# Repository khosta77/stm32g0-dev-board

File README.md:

<h1 align="center">g0_dev_board</h1>

<p align="center">
  Открытая отладочная плата на STM32G0 для разработки
  <a href="https://github.com/khosta77/stm32-sdk">stm32-sdk</a>
  (C++20, только CMSIS, без HAL).
</p>

<p align="center">

</p>

> **Прототип.** Плата ещё не изготавливалась и не проверялась в железе.
> Проект прошёл ERC и DRC, но перед заказом сверьте стек слоёв и ограничения
> выбранного завода (см. раздел «Производство»).

## Назначение

Плата для обкатки драйверов и методологии SDK на STM32G0. Расширения
подключаются через шилды Arduino Uno R3 (CNC Shield V3, модули GSM/Wi-Fi),
все сигналы МК выведены на две гребёнки для логического анализатора.

- Встроенный программатор ST-LINK/V2-1-совместимый (DAPLink или Black Magic Probe)
- USB-UART на USART1, через него же работает ROM-загрузчик STM32G0
- Ethernet 10/100 на W5500, флэш 32 Мбит и microSD на общей шине SPI2
- Два датчика температуры TMP100: на верхней и нижней стороне платы
- Перемычки как на Nucleo: измерение тока МК (JP_IDD), отключение программатора

## Основные характеристики

| Параметр | Значение |
| --- | --- |
| МК | STM32G0B1CCT6 (LQFP-48), pin-to-pin совместим с STM32G071CBT6 |
| Программатор | STM32F103CBT6, USB Mini-B (J201), SWD на МК через JP_SWD 2x3 |
| USB-UART | FT232RL, USB Mini-B (J301) |
| Ethernet | W5500 + RJ45 HR911105A (магнитика в разъёме) |
| Память | W25Q32JVSSIQ (4 МБ) + microSD (Hirose DM3AT), общая SPI2 |
| Датчики | 2x TMP100 на I2C1 (0x4E, 0x4A) |
| Питание | от любого из двух USB через диоды Шоттки, LDO AP7361C-33E на 3.3 В |
| Расширение | разъёмы Arduino Uno R3 (без ICSP), 2 гребёнки ЛА 1x27 |
| Плата | 80 x 114 мм, 4 слоя: сигнал / GND / GND / сигнал |

Полная таблица назначения выводов МК — на листе `scheme/cpu.kicad_sch`
(и в [PDF схемы](docs/schematic.pdf)). Подписи выводов гребёнок ЛА нанесены
на шелкографию в формате «сигнал + порт МК».

## Содержимое репозитория

- `g0_dev_board.kicad_pro`, `g0_dev_board.kicad_sch`, `scheme/` — схема
  (KiCad 10, 8 листов)
- `g0_dev_board.kicad_pcb`, `g0_dev_board.kicad_dru` — плата и
  дополнительные правила DRC
- `g0_dev_board.kicad_sym`, `g0_dev_board.pretty/` — проектные библиотеки
- [`manufacturing/`](manufacturing/) — Gerber, сверловка, BOM и CPL в формате JLCPCB
- [`docs/`](docs/) — [PDF схемы](docs/schematic.pdf) и изображение платы
- [`scripts/export_manufacturing.py`](scripts/export_manufacturing.py) —
  генерация всех выгрузок одной командой
- [`RULES.md`](RULES.md) — правила расстановки и трассировки платы
- [`CLAUDE.md`](CLAUDE.md) — состав, соглашения проекта, нюансы для прошивки

## Производство

Файлы в `manufacturing/` подготовлены под JLCPCB и подходят большинству
заводов:

- `gerber/` — медь F/In1/In2/B, маска, паста, шелкография, контур,
  сверловка PTH/NPTH (Excellon) с картами отверстий;
- `BOM-g0_dev_board.csv` — колонки `Comment, Designator, Footprint, LCSC Part #`;
- `CPL-g0_dev_board.csv` — колонки `Designator, Mid X, Mid Y, Layer, Rotation`.

Перед заказом:

- **Стек и ограничения завода.** Переходные отверстия 0.4/0.3 мм, зазор
  0.2 мм, дорожки от 0.3 мм. Ширины дифпар USB (90 Ом) и MDI (100 Ом)
  нужно сверить со стеком выбранного завода.
- **Нижняя сторона.** U602 и C602 стоят на нижней стороне: при заводском
  монтаже нужна сборка второй стороны, иначе их паяют вручную.
- **Коды LCSC не заданы** для J201/J301 (USB Mini-B), J805/J806 (гребёнки 1x27)
  и JP801 (2x3) — подберите их или ставьте эти разъёмы вручную.
- **Не устанавливаются (DNP):** C109, C301, C701, R703 — в BOM и CPL их нет.
- **Повороты в CPL** взяты из KiCad. Для части корпусов нулевой угол JLCPCB
  отличается от KiCad — проверьте ориентацию в предпросмотре сборки на
  сайте завода.

## Лицензия

Оригинальные исходники проекта распространяются под
[CERN Open Hardware Licence Version 2 - Permissive](LICENSE) (CERN-OHL-P v2).
Источник: <https://github.com/khosta77/stm32g0-dev-board>.

Символы и посадочные места из библиотек KiCad распространяются на своих
условиях — см. [NOTICE](NOTICE) и [THIRD-PARTY-NOTICES.md](THIRD-PARTY-NOTICES.md).
Изменения проекта записываются в [CHANGES.txt](CHANGES.txt), авторы — в
[AUTHORS.md](AUTHORS.md), порядок участия — в [CONTRIBUTING.md](CONTRIBUTING.md).

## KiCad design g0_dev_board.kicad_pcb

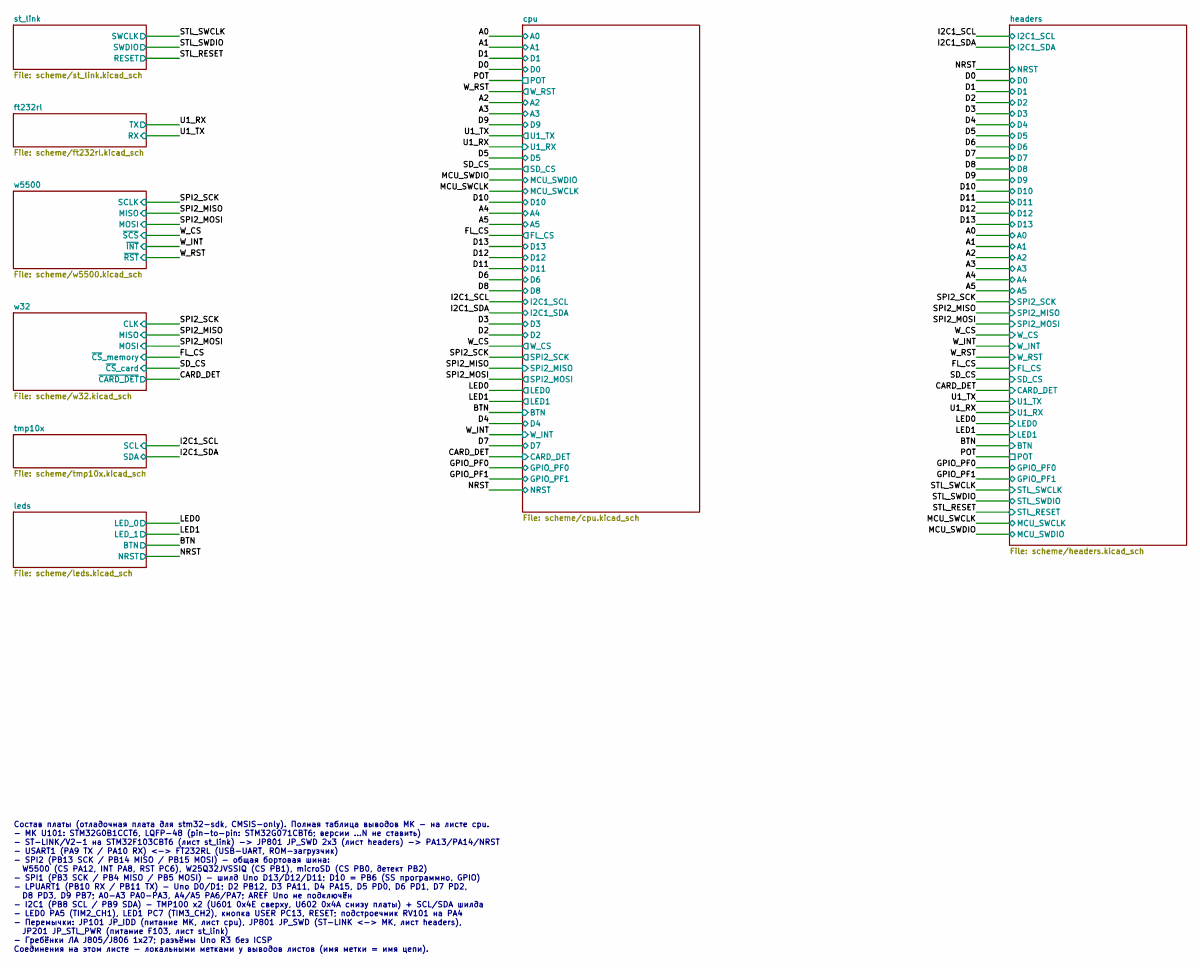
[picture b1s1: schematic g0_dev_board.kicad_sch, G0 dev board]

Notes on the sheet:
Состав платы (отладочная плата для stm32-sdk, CMSIS-only). Полная таблица выводов МК - на листе cpu. - МК U101: STM32G0B1CCT6, LQFP-48 (pin-to-pin: STM32G071CBT6; версии ...N не ставить) - ST-LINK/V2-1 на STM32F103CBT6 (лист st_link) -> JP801 JP_SWD 2x3 (лист headers) -> PA13/PA14/NRST - USART1 (PA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

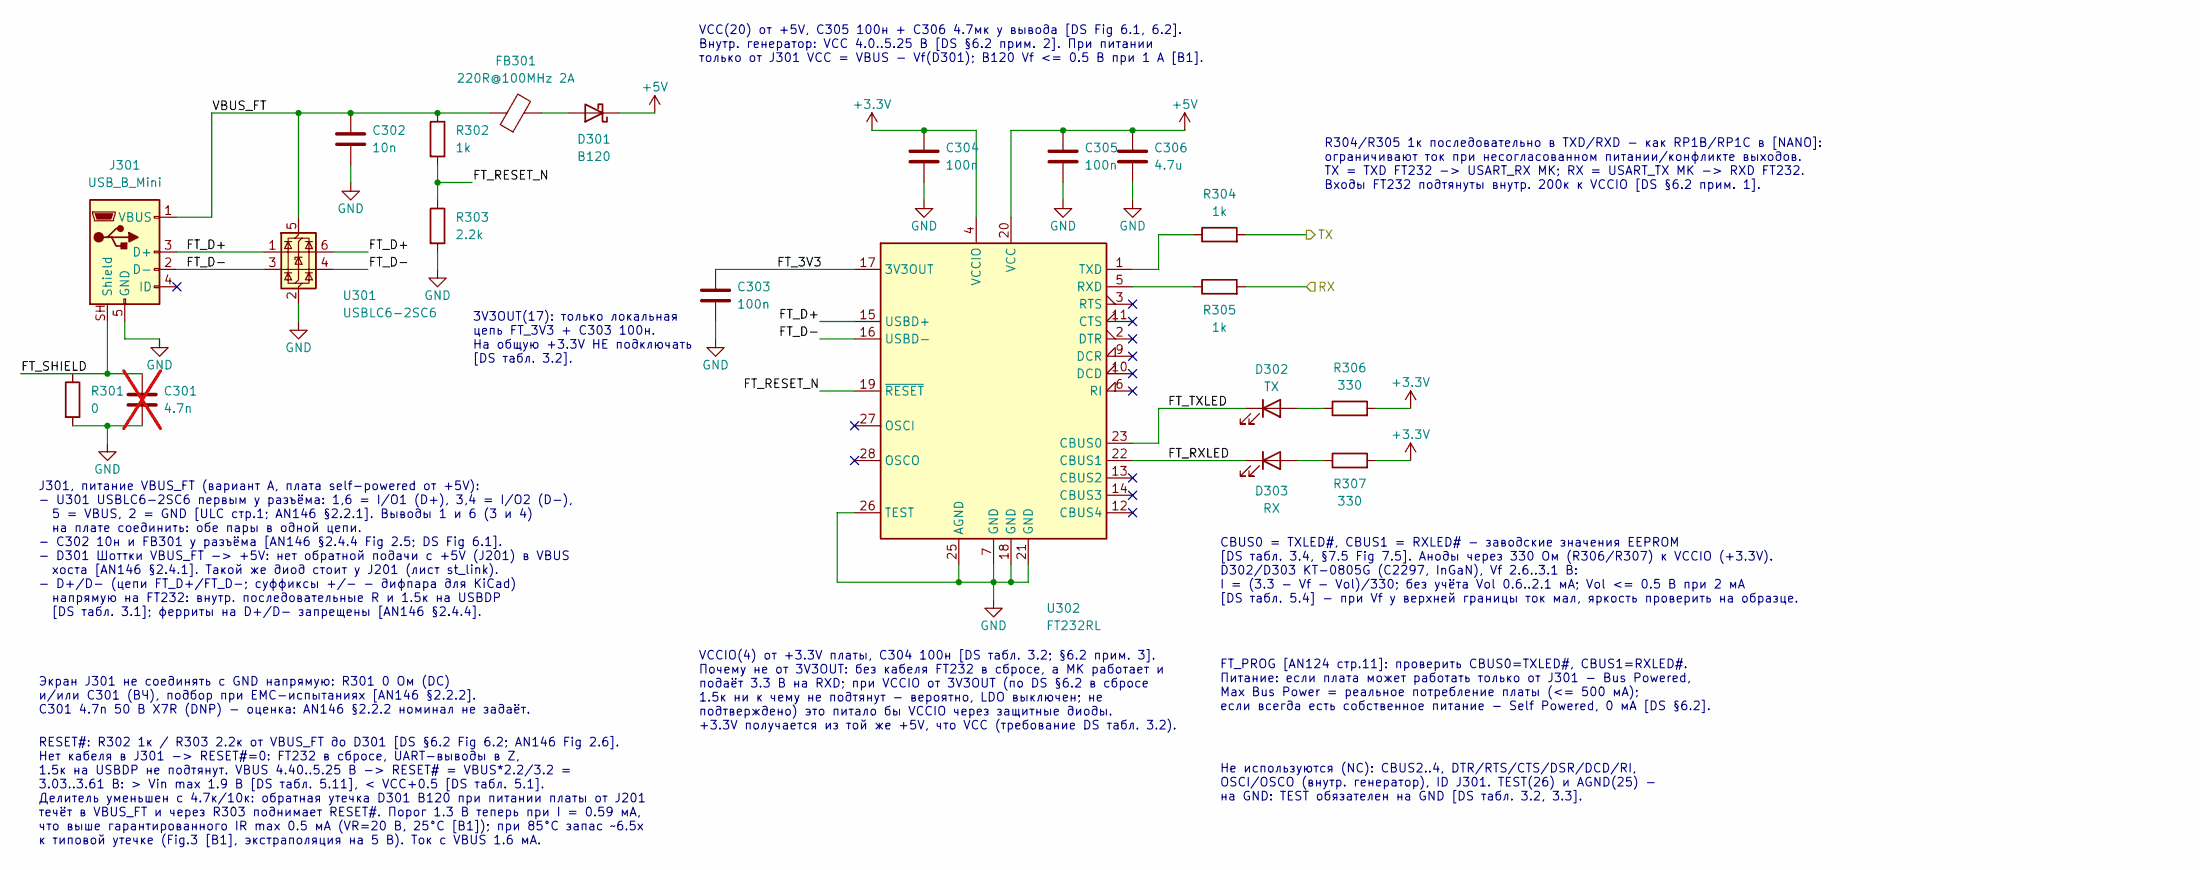
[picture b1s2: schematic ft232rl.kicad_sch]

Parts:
C301: 4.7n; C_0805_2012Metric; LCSC C1744; not fitted
C302: 10n; C_0805_2012Metric; LCSC C1710
C303, C304, C305: 100n; C_0805_2012Metric; LCSC C49678
C306: 4.7u; C_0805_2012Metric; LCSC C1779
D301: B120; D_SMA; MPN B120-13-F; LCSC C134421
D302: TX; LED_0805_2012Metric; LCSC C2297
D303: RX; LED_0805_2012Metric; LCSC C2297
FB301: 220R@100MHz 2A; L_0805_2012Metric; MPN BLM21PG221SN1D; LCSC C85840
J301: USB_B_Mini; USB_Mini-B_Lumberg_2486_01_Horizontal
R301: 0; R_0805_2012Metric; LCSC C17477
R302, R304, R305: 1k; R_0805_2012Metric; LCSC C17513
R303: 2.2k; R_0805_2012Metric; LCSC C17520
R306, R307: 330; R_0805_2012Metric; LCSC C17630
U301: USBLC6-2SC6; SOT-23-6; MPN USBLC6-2SC6; LCSC C7519
U302: FT232RL; SSOP-28_5.3x10.2mm_P0.65mm; LCSC C8690

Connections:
+3.3V: C304.1, R306.2, R307.2, U302.4 (VCCIO); also elsewhere on the board
+5V: C305.1, C306.1, D301.1 (K), U302.20 (VCC); also elsewhere on the board
/U1_RX: R304.2; also elsewhere on the board
/U1_TX: R305.2; also elsewhere on the board
/ft232rl/FT_3V3: C303.1, U302.17 (3V3OUT)
/ft232rl/FT_D+: J301.3 (D+), U301.1 (I/O1), U301.6 (I/O1), U302.15 (USBD+)
/ft232rl/FT_D-: J301.2 (D-), U301.3 (I/O2), U301.4 (I/O2), U302.16 (USBD-)
/ft232rl/FT_RESET_N: R302.2, R303.1, U302.19 (~RESET)
/ft232rl/FT_RXLED: D303.1 (K), U302.22 (CBUS1)
/ft232rl/FT_SHIELD: C301.1, J301.SH (Shield), R301.1
/ft232rl/FT_TXLED: D302.1 (K), U302.23 (CBUS0)
/ft232rl/VBUS_FT: C302.1, FB301.1, J301.1 (VBUS), R302.1, U301.5 (VBUS)
GND: C301.2, C302.2, C303.2, C304.2, C305.2, C306.2, J301.5 (GND), R301.2, R303.2, U301.2 (GND), U302.7 (GND), U302.18 (GND), U302.21 (GND), U302.25 (AGND), U302.26 (TEST); also elsewhere on the board
unnamed: D301.2 (A), FB301.2
unnamed: D302.2 (A), R306.1
unnamed: D303.2 (A), R307.1
unnamed: R305.1, U302.5 (RXD)
unnamed: R304.1, U302.1 (TXD)

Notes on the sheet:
RESET#: R302 1к / R303 2.2к от VBUS_FT до D301 [DS §6.2 Fig 6.2; AN146 Fig 2.6]. Нет кабеля в J301 -> RESET#=0: FT232 в сбросе, UART-выводы в Z, 1.5к на USBDP не подтянут. VBUS 4.40..5.25 В -> RESET# = VBUS*2.2/3.2 = 3.03..3.61 В: > Vin max 1.9 В [DS табл. 5.11], < VCC+0.5 [DS табл. 5.1]. Делитель 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
R304/R305 1к последовательно в TXD/RXD - как RP1B/RP1C в [NANO]: ограничивают ток при несогласованном питании/конфликте выходов. TX = TXD FT232 -> USART_RX МК; RX = USART_TX МК -> RXD FT232. Входы FT232 подтянуты внутр. 200к к VCCIO [DS §6.2 прим. 1].
3V3OUT(17): только локальная цепь FT_3V3 + C303 100н. На общую +3.3V НЕ подключать [DS табл. 3.2].
VCCIO(4) от +3.3V платы, C304 100н [DS табл. 3.2; §6.2 прим. 3]. Почему не от 3V3OUT: без кабеля FT232 в сбросе, а МК работает и подаёт 3.3 В на RXD; при VCCIO от 3V3OUT (по DS §6.2 в сбросе 1.5к ни к чему не подтянут - вероятно, LDO выключен; не подтверждено) это питало бы VCCIO через защитные дио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
VCC(20) от +5V, C305 100н + C306 4.7мк у вывода [DS Fig 6.1, 6.2]. Внутр. генератор: VCC 4.0..5.25 В [DS §6.2 прим. 2]. При питании только от J301 VCC = VBUS - Vf(D301); B120 Vf <= 0.5 В при 1 А [B1].
FT_PROG [AN124 стр.11]: проверить CBUS0=TXLED#, CBUS1=RXLED#. Питание: если плата может работать только от J301 - Bus Powered, Max Bus Power = реальное потребление платы (<= 500 мА); если всегда есть собственное питание - Self Powered, 0 мА [DS §6.2].
Не используются (NC): CBUS2..4, DTR/RTS/CTS/DSR/DCD/RI, OSCI/OSCO (внутр. генератор), ID J301. TEST(26) и AGND(25) - на GND: TEST обязателен на GND [DS табл. 3.2, 3.3].
J301, питание VBUS_FT (вариант A, плата self-powered от +5V): - U301 USBLC6-2SC6 первым у разъёма: 1,6 = I/O1 (D+), 3,4 = I/O2 (D-), 5 = VBUS, 2 = GND [ULC стр.1; AN146 §2.2.1]. Выводы 1 и 6 (3 и 4) на плате соединить: обе пары в одной цепи. - C302 10н и FB301 у разъёма [AN146 §2.4.4 Fig 2.5; DS Fi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
CBUS0 = TXLED#, CBUS1 = RXLED# - заводские значения EEPROM [DS табл. 3.4, §7.5 Fig 7.5]. Аноды через 330 Ом (R306/R307) к VCCIO (+3.3V). D302/D303 KT-0805G (C2297, InGaN), Vf 2.6..3.1 В: I = (3.3 - Vf - Vol)/330; без учёта Vol 0.6..2.1 мА; Vol <= 0.5 В при 2 мА [DS табл. 5.4] - при Vf у верхней гра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
Экран J301 не соединять с GND напрямую: R301 0 Ом (DC) и/или C301 (ВЧ), подбор при EMC-испытаниях [AN146 §2.2.2]. C301 4.7n 50 В X7R (DNP) - оценка: AN146 §2.2.2 номинал не задаёт.

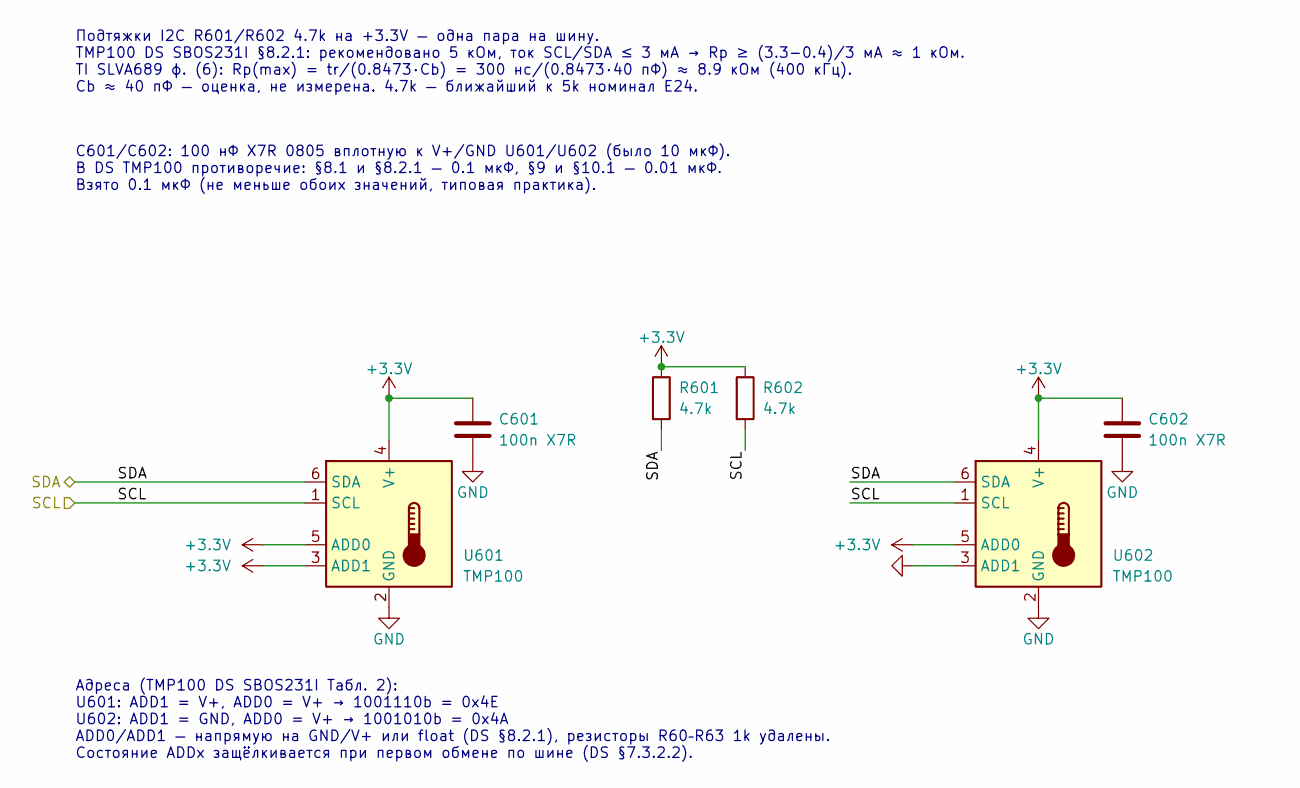
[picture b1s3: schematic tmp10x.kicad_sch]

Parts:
C601, C602: 100n X7R; C_0805_2012Metric; LCSC C49678
R601, R602: 4.7k; R_0805_2012Metric; LCSC C17673
U601, U602: TMP100; SOT-23-6; LCSC C31810

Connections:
+3.3V: C601.1, C602.1, R601.1, R602.1, U601.3 (ADD1), U601.4 (V+), U601.5 (ADD0), U602.4 (V+), U602.5 (ADD0); also elsewhere on the board
/I2C1_SCL: R602.2, U601.1 (SCL), U602.1 (SCL); also elsewhere on the board
/I2C1_SDA: R601.2, U601.6 (SDA), U602.6 (SDA); also elsewhere on the board
GND: C601.2, C602.2, U601.2 (GND), U602.2 (GND), U602.3 (ADD1); also elsewhere on the board

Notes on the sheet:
Подтяжки I2C R601/R602 4.7k на +3.3V — одна пара на шину. TMP100 DS SBOS231I §8.2.1: рекомендовано 5 кОм, ток SCL/SDA ≤ 3 мА → Rp ≥ (3.3−0.4)/3 мА ≈ 1 кОм. TI SLVA689 ф. (6): Rp(max) = tr/(0.8473·Cb) = 300 нс/(0.8473·40 пФ) ≈ 8.9 кОм (400 кГц). Cb ≈ 40 пФ — оценка, не измерена. 4.7k — ближайший к 5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
Адреса (TMP100 DS SBOS231I Табл. 2): U601: ADD1 = V+, ADD0 = V+ → 1001110b = 0x4E U602: ADD1 = GND, ADD0 = V+ → 1001010b = 0x4A ADD0/ADD1 — напрямую на GND/V+ или float (DS §8.2.1), резисторы R60–R63 1k удалены. Состояние ADDx защёлкивается при первом обмене по шине (DS §7.3.2.2).
C601/C602: 100 нФ X7R 0805 вплотную к V+/GND U601/U602 (было 10 мкФ). В DS TMP100 противоречие: §8.1 и §8.2.1 — 0.1 мкФ, §9 и §10.1 — 0.01 мкФ. Взято 0.1 мкФ (не меньше обоих значений, типовая практика).

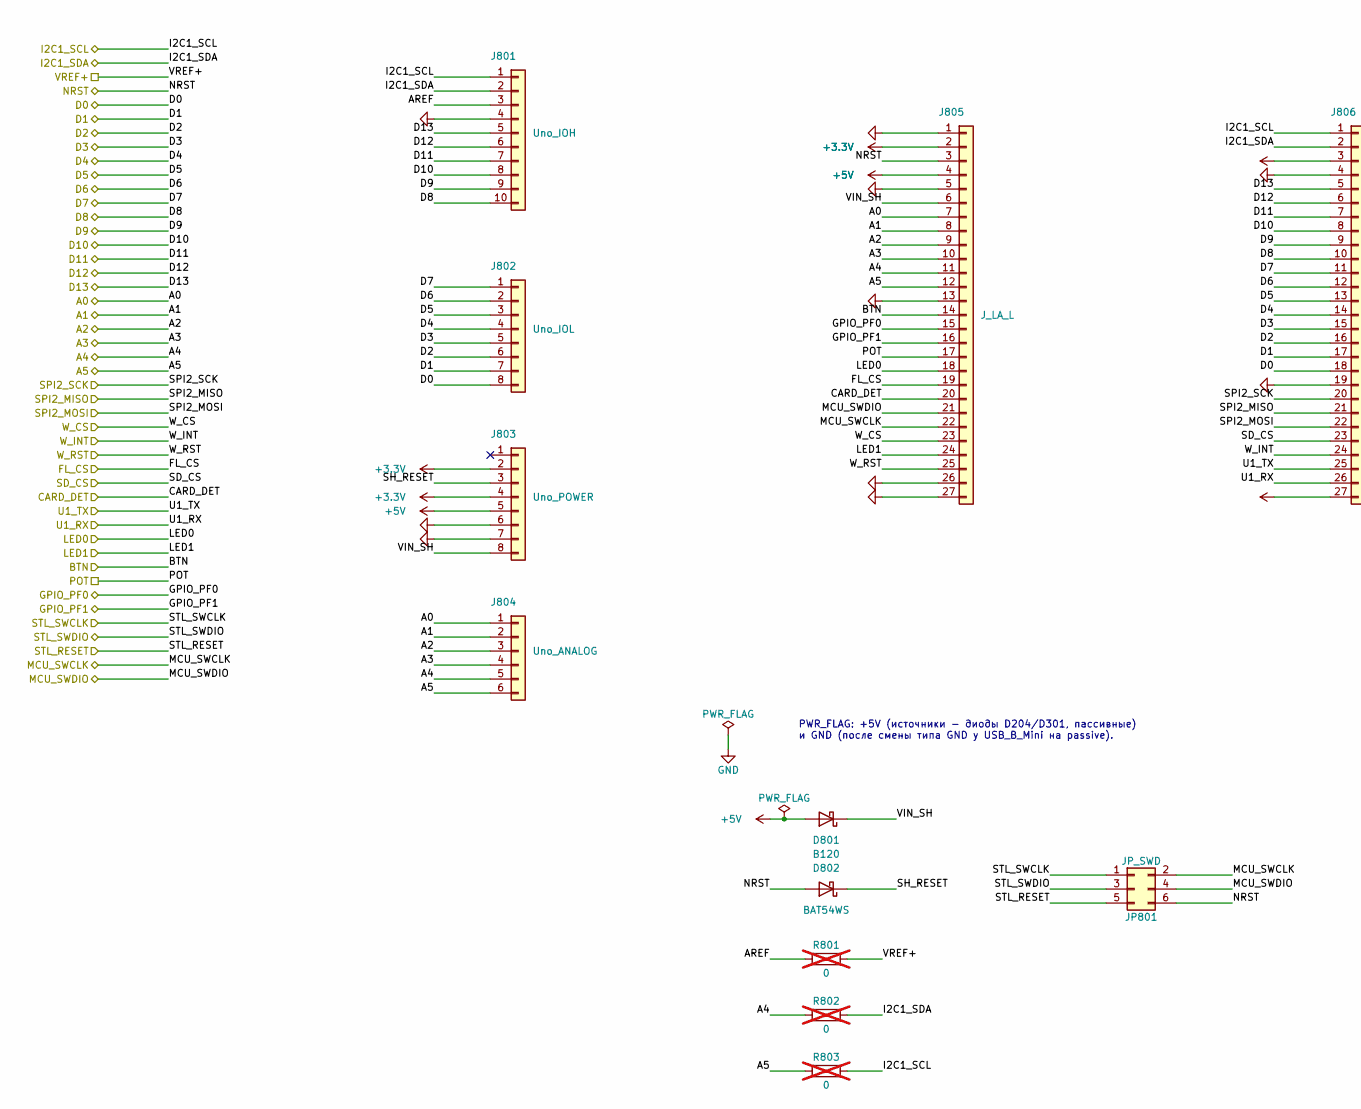
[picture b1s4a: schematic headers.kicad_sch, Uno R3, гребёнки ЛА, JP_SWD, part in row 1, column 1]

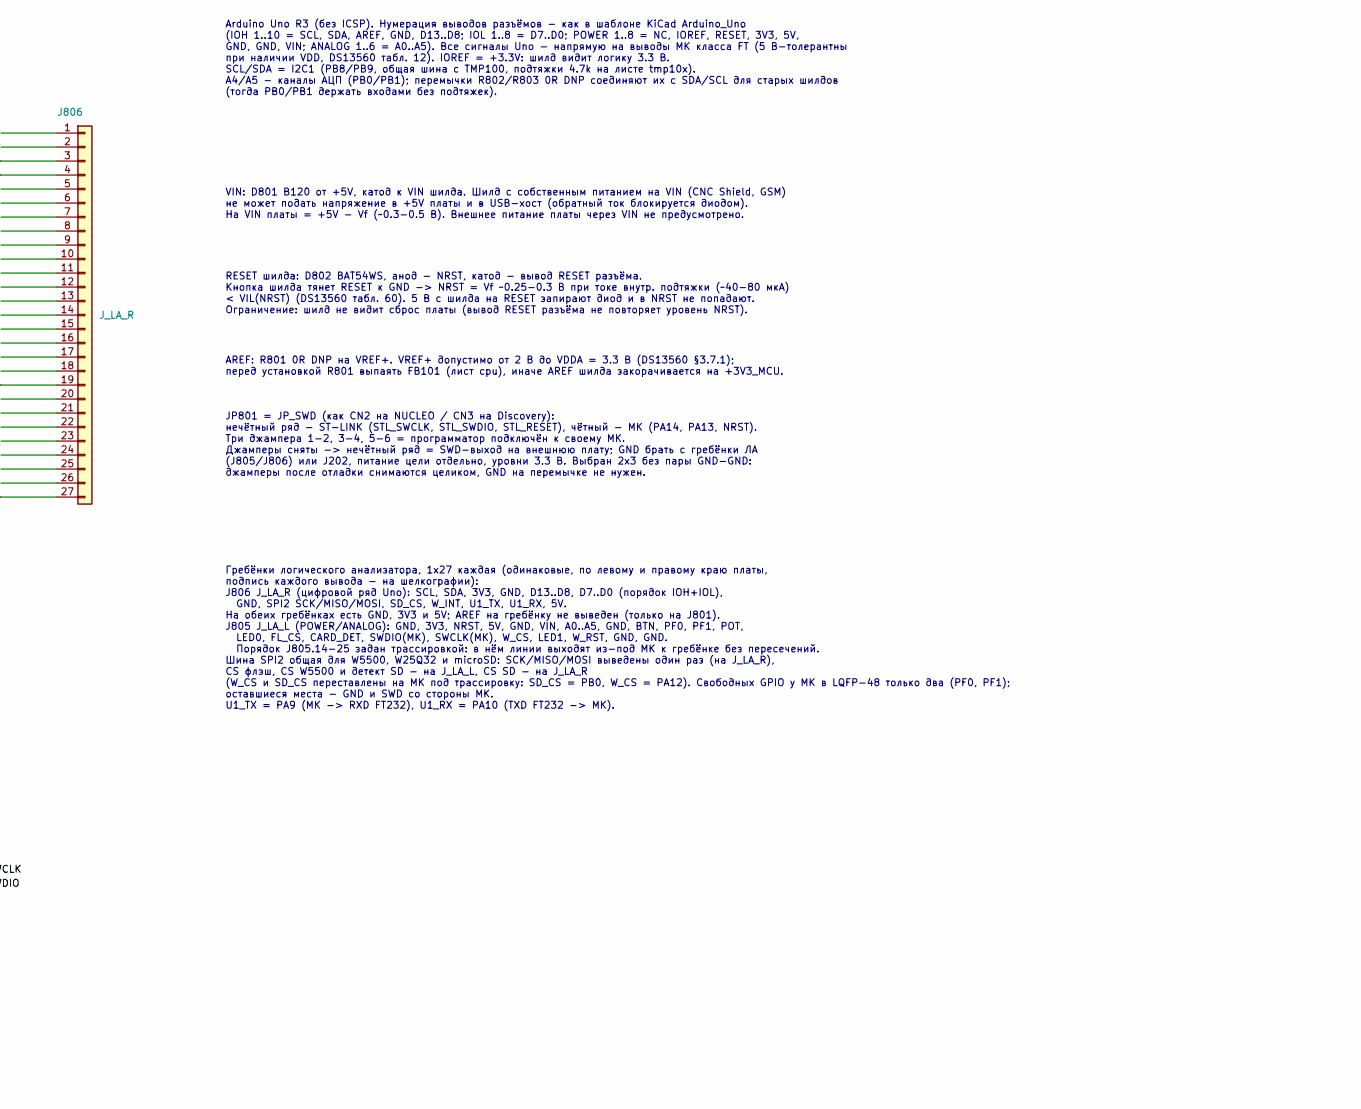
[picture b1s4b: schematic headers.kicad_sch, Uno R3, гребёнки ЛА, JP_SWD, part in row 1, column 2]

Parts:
D801: B120; D_SMA; MPN B120-13-F; LCSC C134421
D802: BAT54WS; D_SOD-323_HandSoldering; MPN BAT54WS; LCSC C124205
J801: Uno_IOH; PinSocket_1x10_P2.54mm_Vertical; LCSC C2905418
J802: Uno_IOL; PinSocket_1x08_P2.54mm_Vertical; LCSC C42431840
J803: Uno_POWER; PinSocket_1x08_P2.54mm_Vertical; LCSC C42431840
J804: Uno_ANALOG; PinSocket_1x06_P2.54mm_Vertical; LCSC C40877
J805: J_LA_L; PinHeader_1x27_P2.54mm_Vertical
J806: J_LA_R; PinHeader_1x27_P2.54mm_Vertical
JP801: JP_SWD; PinHeader_2x03_P2.54mm_Vertical
R801, R802, R803: 0; R_0805_2012Metric; LCSC C17477; not fitted

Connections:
+3.3V: J803.2, J803.4, J805.2, J806.3; also elsewhere on the board
+5V: D801.2 (A), J803.5, J805.4, J806.27; also elsewhere on the board
/A0: J804.1, J805.7; also elsewhere on the board
/A1: J804.2, J805.8; also elsewhere on the board
/A2: J804.3, J805.9; also elsewhere on the board
/A3: J804.4, J805.10; also elsewhere on the board
/A4: J804.5, J805.11, R802.1; also elsewhere on the board
/A5: J804.6, J805.12, R803.1; also elsewhere on the board
/BTN: J805.14; also elsewhere on the board
/CARD_DET: J805.20; also elsewhere on the board
/D0: J802.8, J806.18; also elsewhere on the board
/D1: J802.7, J806.17; also elsewhere on the board
/D2: J802.6, J806.16; also elsewhere on the board
/D3: J802.5, J806.15; also elsewhere on the board
/D4: J802.4, J806.14; also elsewhere on the board
/D5: J802.3, J806.13; also elsewhere on the board
/D6: J802.2, J806.12; also elsewhere on the board
/D7: J802.1, J806.11; also elsewhere on the board
/D8: J801.10, J806.10; also elsewhere on the board
/D9: J801.9, J806.9; also elsewhere on the board
/D10: J801.8, J806.8; also elsewhere on the board
/D11: J801.7, J806.7; also elsewhere on the board
/D12: J801.6, J806.6; also elsewhere on the board
/D13: J801.5, J806.5; also elsewhere on the board
/FL_CS: J805.19; also elsewhere on the board
/GPIO_PF0: J805.15; also elsewhere on the board
/GPIO_PF1: J805.16; also elsewhere on the board
/I2C1_SCL: J801.1, J806.1, R803.2; also elsewhere on the board
/I2C1_SDA: J801.2, J806.2, R802.2; also elsewhere on the board
/LED0: J805.18; also elsewhere on the board
/LED1: J805.24; also elsewhere on the board
/MCU_SWCLK: J805.22, JP801.2; also elsewhere on the board
/MCU_SWDIO: J805.21, JP801.4; also elsewhere on the board
/NRST: D802.2 (A), J805.3, JP801.6; also elsewhere on the board
/POT: J805.17; also elsewhere on the board
/SD_CS: J806.23; also elsewhere on the board
/SPI2_MISO: J806.21; also elsewhere on the board
/SPI2_MOSI: J806.22; also elsewhere on the board
/SPI2_SCK: J806.20; also elsewhere on the board
/STL_RESET: JP801.5; also elsewhere on the board
/STL_SWCLK: JP801.1; also elsewhere on the board
/STL_SWDIO: JP801.3; also elsewhere on the board
/U1_RX: J806.26; also elsewhere on the board
/U1_TX: J806.25; also elsewhere on the board
/W_CS: J805.23; also elsewhere on the board
/W_INT: J806.24; also elsewhere on the board
/W_RST: J805.25; also elsewhere on the board
/headers/SH_RESET: D802.1 (K), J803.3
/headers/VIN_SH: D801.1 (K), J803.8, J805.6
GND: J801.4, J803.6, J803.7, J805.1, J805.5, J805.13, J805.26, J805.27, J806.4, J806.19; also elsewhere on the board
unnamed: J801.3, R801.1

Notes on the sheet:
Гребёнки логического анализатора, 1x27 каждая (одинаковые, по левому и правому краю платы, подпись каждого вывода - на шелкографии): J806 J_LA_R (цифровой ряд Uno): SCL, SDA, 3V3, GND, D13..D8, D7..D0 (порядок IOH+IOL), GND, SPI2 SCK/MISO/MOSI, SD_CS, W_INT, U1_TX, U1_RX, 5V. На обеих гребёнках ест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
Arduino Uno R3 (без ICSP). Нумерация выводов разъёмов - как в шаблоне KiCad Arduino_Uno (IOH 1..10 = SCL, SDA, AREF, GND, D13..D8; IOL 1..8 = D7..D0; POWER 1..8 = NC, IOREF, RESET, 3V3, 5V, GND, GND, VIN; ANALOG 1..6 = A0..A5). Все сигналы Uno - напрямую на выводы МК класса FT (5 В-толерантны при н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
VIN: D801 B120 от +5V, катод к VIN шилда. Шилд с собственным питанием на VIN (CNC Shield, GSM) не может подать напряжение в +5V платы и в USB-хост (обратный ток блокируется диодом). На VIN платы = +5V - Vf (~0.3-0.5 В). Внешнее питание платы через VIN не предусмотрено.
AREF: R801 0R DNP на VREF+. VREF+ допустимо от 2 В до VDDA = 3.3 В (DS13560 §3.7.1); перед установкой R801 выпаять FB101 (лист cpu), иначе AREF шилда закорачивается на +3V3_MCU.
PWR_FLAG: +5V (источники - диоды D204/D301, пассивные) и GND (после смены типа GND у USB_B_Mini на passive).
RESET шилда: D802 BAT54WS, анод - NRST, катод - вывод RESET разъёма. Кнопка шилда тянет RESET к GND -> NRST = Vf ~0.25-0.3 В при токе внутр. подтяжки (~40-80 мкА) < VIL(NRST) (DS13560 табл. 60). 5 В с шилда на RESET запирают диод и в NRST не попадают. Ограничение: шилд не видит сброс платы (вывод R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
JP801 = JP_SWD (как CN2 на NUCLEO / CN3 на Discovery): нечётный ряд - ST-LINK (STL_SWCLK, STL_SWDIO, STL_RESET), чётный - МК (PA14, PA13, NRST). Три джампера 1-2, 3-4, 5-6 = программатор подключён к своему МК. Джамперы сняты -> нечётный ряд = SWD-выход на внешнюю плату; GND брать с гребёнки ЛА (J80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

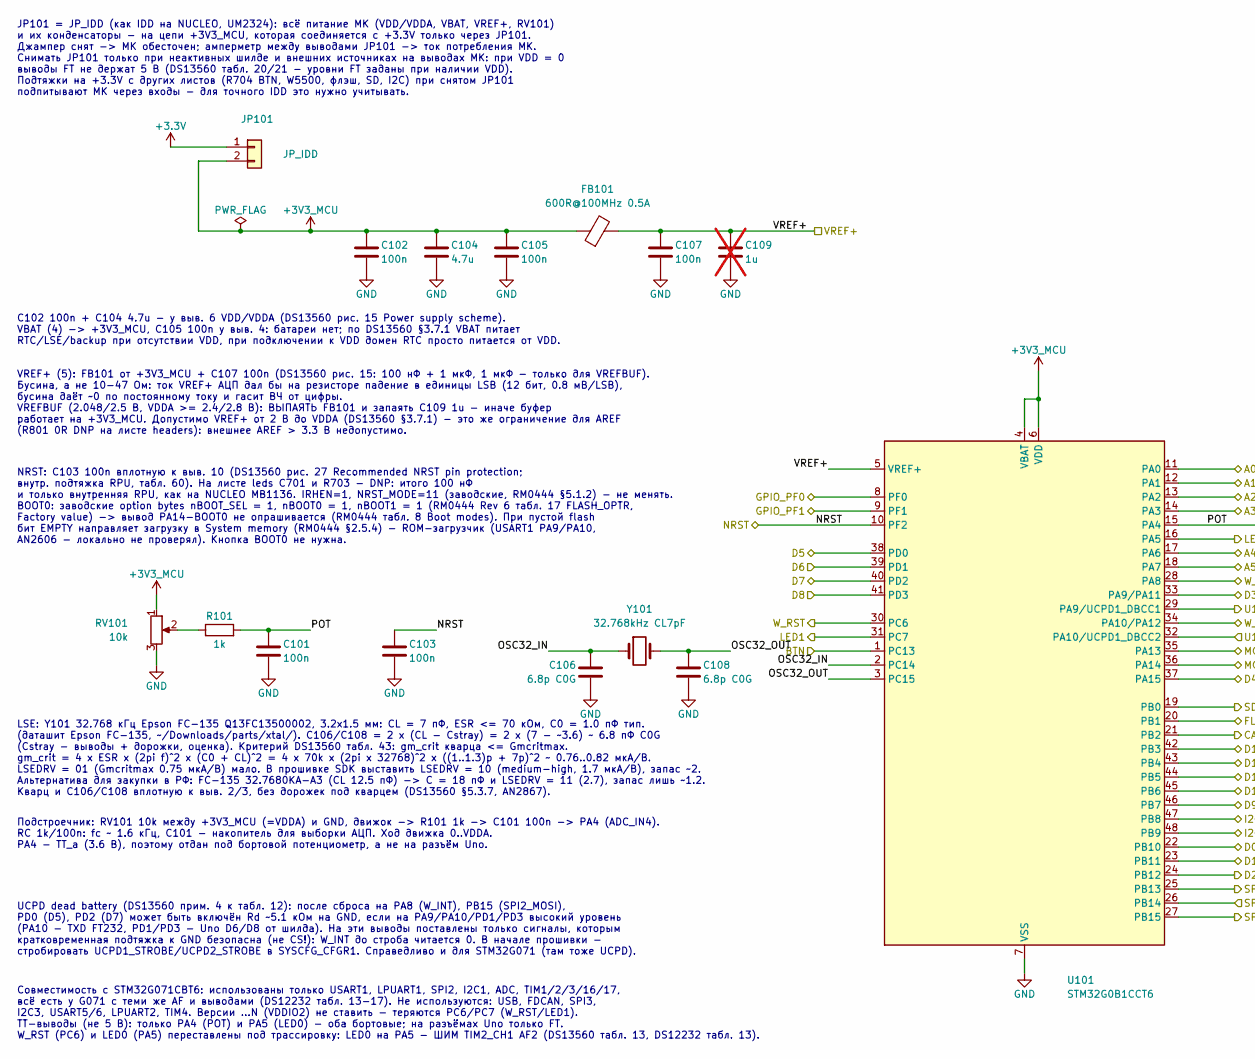
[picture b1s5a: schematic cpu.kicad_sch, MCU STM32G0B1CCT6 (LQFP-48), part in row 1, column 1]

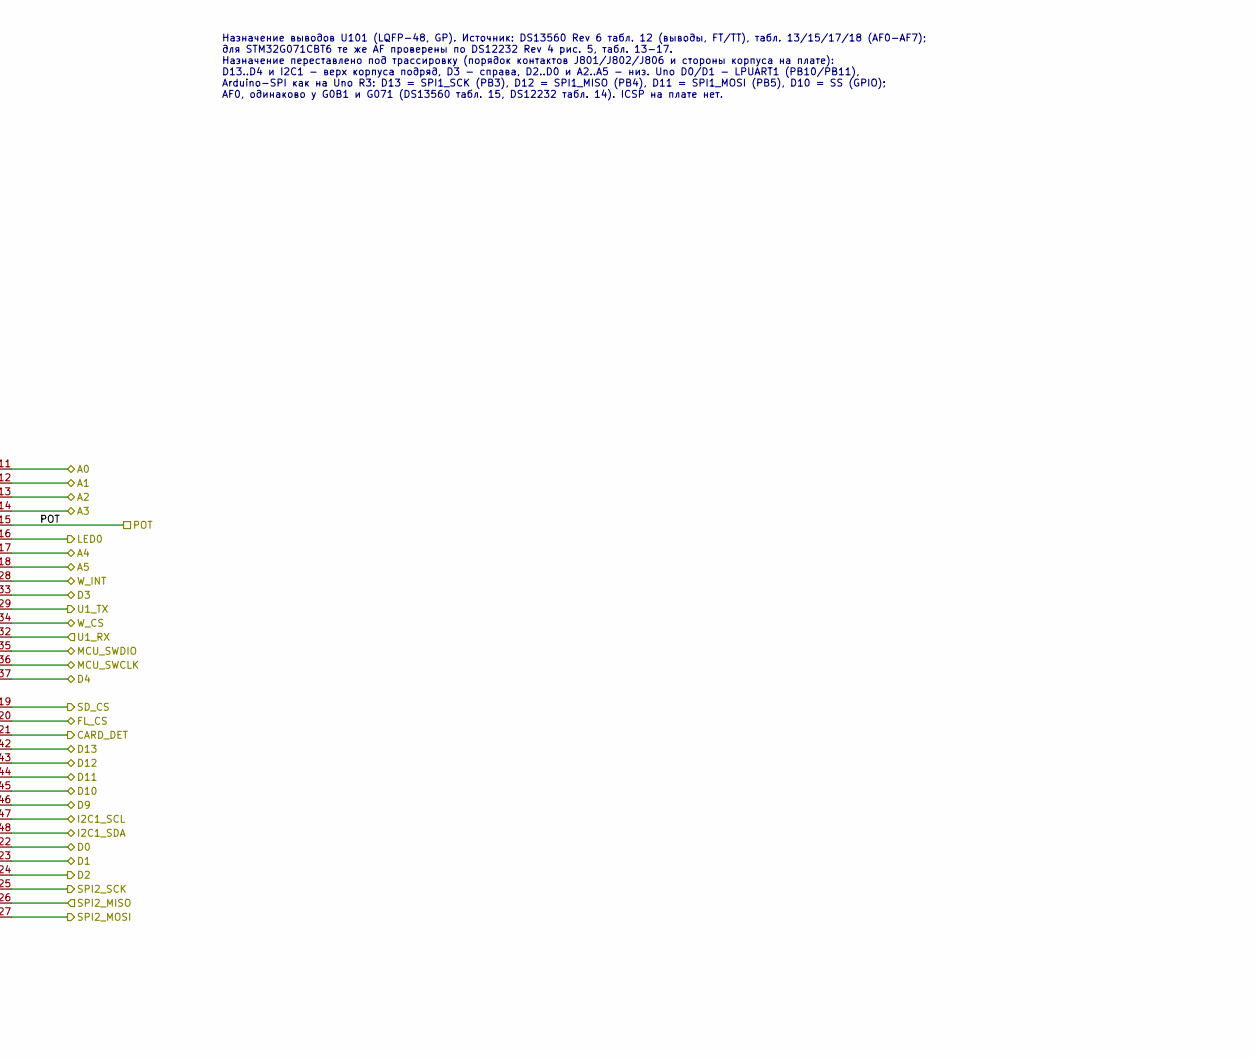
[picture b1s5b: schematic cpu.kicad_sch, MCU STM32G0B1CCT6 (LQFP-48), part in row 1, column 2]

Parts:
C101, C102, C103, C105, C107: 100n; C_0805_2012Metric; LCSC C49678
C104: 4.7u; C_0805_2012Metric; LCSC C1779
C106, C108: 6.8p C0G; C_0805_2012Metric; LCSC C1832
C109: 1u; C_0805_2012Metric; LCSC C28323; not fitted
FB101: 600R@100MHz 0.5A; L_0805_2012Metric; MPN GZ2012D601TF; LCSC C1017
JP101: JP_IDD; PinHeader_1x02_P2.54mm_Vertical; LCSC C42431798
R101: 1k; R_0805_2012Metric; LCSC C17513
RV101: 10k; Potentiometer_Bourns_3314J_Vertical; MPN 3314J-1-103E; LCSC C36376
U101: STM32G0B1CCT6; LQFP-48_7x7mm_P0.5mm; MPN STM32G0B1CCT6; LCSC C5270241
Y101: 32.768kHz CL7pF; Crystal_SMD_G8-2Pin_3.2x1.5mm_HandSoldering; MPN Q13FC13500002; LCSC C48615

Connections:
+3.3V: JP101.1; also elsewhere on the board
+3V3_MCU: C102.1, C104.1, C105.1, FB101.1, JP101.2, RV101.1, U101.4 (VBAT), U101.6 (VDD)
/A0: U101.11 (PA0); also elsewhere on the board
/A1: U101.12 (PA1); also elsewhere on the board
/A2: U101.13 (PA2); also elsewhere on the board
/A3: U101.14 (PA3); also elsewhere on the board
/A4: U101.17 (PA6); also elsewhere on the board
/A5: U101.18 (PA7); also elsewhere on the board
/BTN: U101.1 (PC13); also elsewhere on the board
/CARD_DET: U101.21 (PB2); also elsewhere on the board
/D0: U101.22 (PB10); also elsewhere on the board
/D1: U101.23 (PB11); also elsewhere on the board
/D2: U101.24 (PB12); also elsewhere on the board
/D3: U101.33 (PA9/PA11); also elsewhere on the board
/D4: U101.37 (PA15); also elsewhere on the board
/D5: U101.38 (PD0); also elsewhere on the board
/D6: U101.39 (PD1); also elsewhere on the board
/D7: U101.40 (PD2); also elsewhere on the board
/D8: U101.41 (PD3); also elsewhere on the board
/D9: U101.46 (PB7); also elsewhere on the board
/D10: U101.45 (PB6); also elsewhere on the board
/D11: U101.44 (PB5); also elsewhere on the board
/D12: U101.43 (PB4); also elsewhere on the board
/D13: U101.42 (PB3); also elsewhere on the board
/FL_CS: U101.20 (PB1); also elsewhere on the board
/GPIO_PF0: U101.8 (PF0); also elsewhere on the board
/GPIO_PF1: U101.9 (PF1); also elsewhere on the board
/I2C1_SCL: U101.47 (PB8); also elsewhere on the board
/I2C1_SDA: U101.48 (PB9); also elsewhere on the board
/LED0: U101.16 (PA5); also elsewhere on the board
/LED1: U101.31 (PC7); also elsewhere on the board
/MCU_SWCLK: U101.36 (PA14); also elsewhere on the board
/MCU_SWDIO: U101.35 (PA13); also elsewhere on the board
/NRST: C103.1, U101.10 (PF2); also elsewhere on the board
/POT: C101.1, R101.2, U101.15 (PA4); also elsewhere on the board
/SD_CS: U101.19 (PB0); also elsewhere on the board
/SPI2_MISO: U101.26 (PB14); also elsewhere on the board
/SPI2_MOSI: U101.27 (PB15); also elsewhere on the board
/SPI2_SCK: U101.25 (PB13); also elsewhere on the board
/U1_RX: U101.32 (PA10/UCPD1_DBCC2); also elsewhere on the board
/U1_TX: U101.29 (PA9/UCPD1_DBCC1); also elsewhere on the board
/W_CS: U101.34 (PA10/PA12); also elsewhere on the board
/W_INT: U101.28 (PA8); also elsewhere on the board
/W_RST: U101.30 (PC6); also elsewhere on the board
/cpu/OSC32_IN: C106.1, U101.2 (PC14), Y101.1
/cpu/OSC32_OUT: C108.1, U101.3 (PC15), Y101.2
/cpu/VREF+: C107.1, C109.1, FB101.2, U101.5 (VREF+)
GND: C101.2, C102.2, C103.2, C104.2, C105.2, C106.2, C107.2, C108.2, C109.2, RV101.3, U101.7 (VSS); also elsewhere on the board
unnamed: R101.1, RV101.2

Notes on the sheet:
VREF+ (5): FB101 от +3V3_MCU + C107 100n (DS13560 рис. 15: 100 нФ + 1 мкФ, 1 мкФ - только для VREFBUF). Бусина, а не 10-47 Ом: ток VREF+ АЦП дал бы на резисторе падение в единицы LSB (12 бит, 0.8 мВ/LSB), бусина даёт ~0 по постоянному току и гасит ВЧ от цифры. VREFBUF (2.048/2.5 В, VDDA >= 2.4/2.8 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
Назначение выводов U101 (LQFP-48, GP). Источник: DS13560 Rev 6 табл. 12 (выводы, FT/TT), табл. 13/15/17/18 (AF0-AF7); для STM32G071CBT6 те же AF проверены по DS12232 Rev 4 рис. 5, табл. 13-17. Назначение переставлено под трассировку (порядок контактов J801/J802/J806 и стороны корпуса на плате): D13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
Совместимость с STM32G071CBT6: использованы только USART1, LPUART1, SPI2, I2C1, ADC, TIM1/2/3/16/17, всё есть у G071 с теми же AF и выводами (DS12232 табл. 13-17). Не используются: USB, FDCAN, SPI3, I2C3, USART5/6, LPUART2, TIM4. Версии ...N (VDDIO2) не ставить - теряются PC6/PC7 (W_RST/LED1). TT-в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
Подстроечник: RV101 10k между +3V3_MCU (=VDDA) и GND, движок -> R101 1k -> C101 100n -> PA4 (ADC_IN4). RC 1k/100n: fc ~ 1.6 кГц, C101 - накопитель для выборки АЦП. Ход движка 0..VDDA. PA4 - TT_a (3.6 В), поэтому отдан под бортовой потенциометр, а не на разъём Uno.
C102 100n + C104 4.7u - у выв. 6 VDD/VDDA (DS13560 рис. 15 Power supply scheme). VBAT (4) -> +3V3_MCU, C105 100n у выв. 4: батареи нет; по DS13560 §3.7.1 VBAT питает RTC/LSE/backup при отсутствии VDD, при подключении к VDD домен RTC просто питается от VDD.
NRST: C103 100n вплотную к выв. 10 (DS13560 рис. 27 Recommended NRST pin protection; внутр. подтяжка RPU, табл. 60). На листе leds C701 и R703 - DNP: итого 100 нФ и только внутренняя RPU, как на NUCLEO MB1136. IRHEN=1, NRST_MODE=11 (заводские, RM0444 §5.1.2) - не менять. BOOT0: заводские option byt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
JP101 = JP_IDD (как IDD на NUCLEO, UM2324): всё питание МК (VDD/VDDA, VBAT, VREF+, RV101) и их конденсаторы - на цепи +3V3_MCU, которая соединяется с +3.3V только через JP101. Джампер снят -> МК обесточен; амперметр между выводами JP101 -> ток потребления МК. Снимать JP101 только при неактивных шил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
LSE: Y101 32.768 кГц Epson FC-135 Q13FC13500002, 3.2x1.5 мм: CL = 7 пФ, ESR <= 70 кОм, C0 = 1.0 пФ тип. (даташит Epson FC-135, ~/Downloads/parts/xtal/). C106/C108 = 2 x (CL - Cstray) = 2 x (7 - ~3.6) ~ 6.8 пФ C0G (Cstray - выводы + дорожки, оценка). Критерий DS13560 табл. 43: gm_crit кварца <= Gmcr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
UCPD dead battery (DS13560 прим. 4 к табл. 12): после сброса на PA8 (W_INT), PB15 (SPI2_MOSI), PD0 (D5), PD2 (D7) может быть включён Rd ~5.1 кОм на GND, если на PA9/PA10/PD1/PD3 высокий уровень (PA10 - TXD FT232, PD1/PD3 - Uno D6/D8 от шилда). На эти выводы поставлены только сигналы, которым кратко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
